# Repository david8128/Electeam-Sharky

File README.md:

# Electeam-Sharky-ESP32

## OrderMe:
1N4728A: caída de voltaje de 3 a 3.5V - CONFIRMAR
## ORDERED:
This is the firmware for the ESP32-DEVKITV1 microcontroller where throttle, break, LCD screen, motor and more systems are integrated.

<!-- TODO Update schematic here -->
> The PCB Kicad folder is located in (controller_bldc_kicad_Sch_PCB/)[https://github.com/david8128/Electeam-Sharky-ESP32/tree/main/controller_bldc_kicad_Sch_PCB]
## Electrical Specifications for the PCB electronics
<!-- Note the reference of nextion in README, 70mA -->
<!-- TODO Document the current and voltage in Current Sensor -->

<!-- TODO Add the MCU and SMPS specs in README-->
#### Power 
Relay for the Operator Presence Control - aka. Death Man Security System (HAT901 12VDC 20A) = 0.96 W
>MOSFET has been considered for de OPC but the consumtion is higher (Using IRF1010N with a )
For this project is used the MCPWM BLDC motor control (hall sensor feedback) example from ESP-IDF library.

As shown in Schematic there were used two [LM2596 DC-DC HW-411](http://tpelectronic.ir/datasheets/20150123144301750.pdf) converters 

#### Battery
When battery is fully charged the voltage is 40.6V. The BMS open the discharging circuit when the battery voltage is under 32V. 

The energy or maximum energetic storage capacity of the battery is 320Wh.

*This modes will be reviewed under the light of the Shell Echo Marathon Competition.*
## Modes

### Acceleration Optimized

### Soft Start

### Manual

Here you have the documentation of the MCPWM-Hall_Sensor example:

## MCPWM BLDC motor control(hall sensor feedback) Example

This example will show you how to use MCPWM module to control bldc motor with hall sensor feedback
 
The following examples uses MCPWM module to control bldc motor and vary its speed continuously

The bldc motor used for testing this code had hall sensor capture sequence of 6-->4-->5-->1-->3-->2-->6-->4--> and so on

IR2103 3-ph bridge driver is used for testing this example code

User needs to make changes according to the motor and gate driver ic used

## Step 1: Pin assignment
* The gpio init function initializes:
	* GPIO19 is assigned as the MCPWM signal for 1H(UH)
	* GPIO18 is assigned as the MCPWM signal for 1L(UL)
	* GPIO17 is assigned as the MCPWM signal for 2H(VH)
	* GPIO16 is assigned as the MCPWM signal for 2L(VL)
	* GPIO15 is assigned as the MCPWM signal for 3H(WH)
	* GPIO14 is assigned as the MCPWM signal for 3L(WL)
	* GPIO23 is assigned as the MCPWM capture signal for Hall A
	* GPIO25 is assigned as the MCPWM capture signal for HALL B
	* GPIO26 is assigned as the MCPWM capture signal for HALL C

## Step 2: Initialize MCPWM
 * You need to set the frequency and duty cycle of MCPWM timer
 * You need to set the MCPWM channel you want to use, and bind the channel with one of the timers
 * You need to set the capture unit, for POS/NEG edge capture
 * Also reversing the hall sensor BIT weight, will make bldc motor rotate CW or CCW

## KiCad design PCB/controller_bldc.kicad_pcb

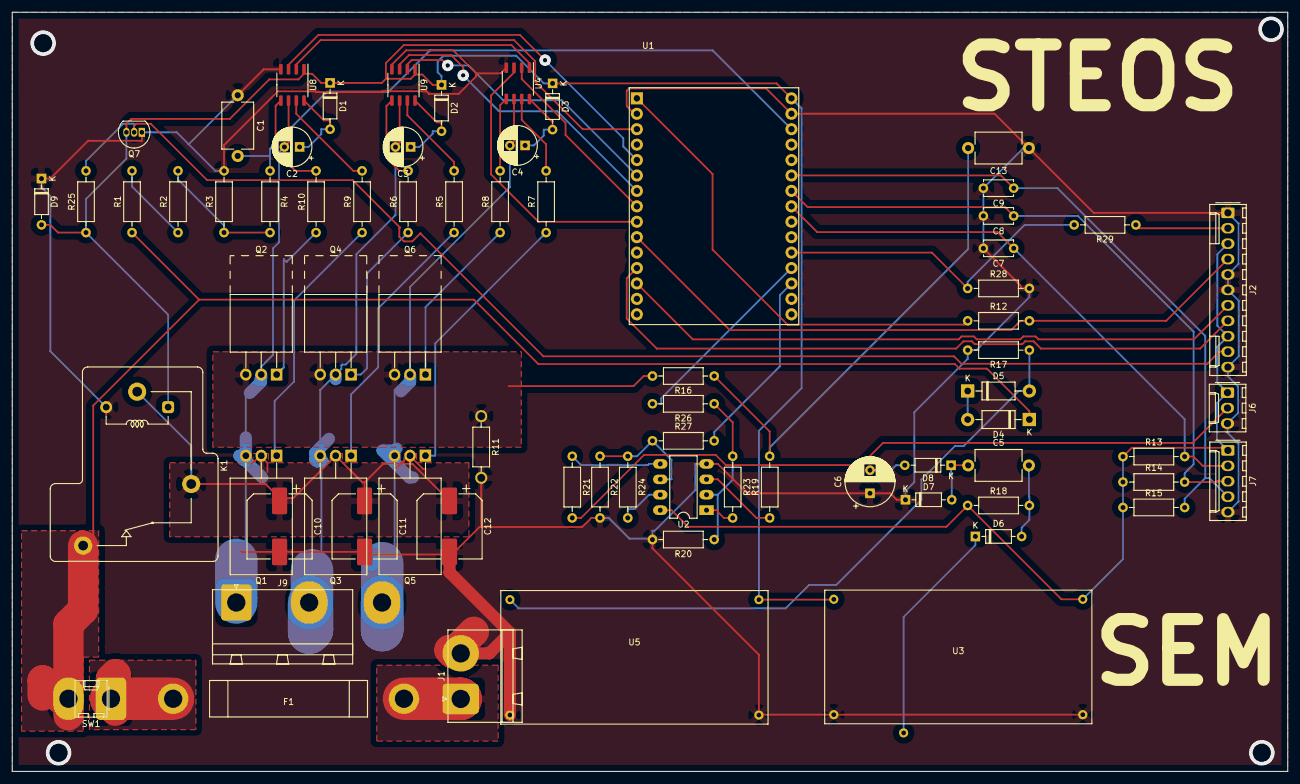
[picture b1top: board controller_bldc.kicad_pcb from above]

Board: 2 copper layers, 210.0 x 125.0 mm, 73 parts (0 on the bottom side), 61 nets.

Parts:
C1: 1uF; C_Disc_D7.5mm_W5.0mm_P10.00mm
C2, C3, C4: 2.2uF; CP_Radial_D6.3mm_P2.50mm
C5: 0.47uF; C_Disc_D7.5mm_W5.0mm_P10.00mm
C6: 47uF; CP_Radial_D8.0mm_P3.80mm
C7, C8, C9: 0.1uF; C_Disc_D4.7mm_W2.5mm_P5.00mm
C10, C11, C12: 220uF; CP_Elec_10x14.3
C13: 0.1uF; C_Disc_D7.5mm_W5.0mm_P10.00mm
D1, D2, D3, D9: 1N4004; D_DO-35_SOD27_P7.62mm_Horizontal
D4, D5: 1N4728A; D_DO-41_SOD81_P10.16mm_Horizontal
D6, D7, D8: 1N4148; D_DO-35_SOD27_P7.62mm_Horizontal
F1: Fuse; Portafusible
J1: Battery Supply; PhoenixContact_GMSTBA_2,5_2-G_1x02_P7.50mm_Horizontal
J2: Conn_01x11_Male; Molex_KK-254_AE-6410-11A_1x11_P2.54mm_Vertical
J6: LM35; Molex_KK-254_AE-6410-03A_1x03_P2.54mm_Vertical
J7: Hall Sensors; Molex_KK-254_AE-6410-05A_1x05_P2.54mm_Vertical
J9: BLDC Motor; PhoenixContact_GMSTBA_2,5_3-G-7,62_1x03_P7.62mm_Horizontal
K1: RAYEX-L90B; Relay_SPST_RAYEX-L90B
Q1, Q3, Q5: IRF1010N; TO-220-3_Horizontal_TabDown
Q2, Q4, Q6: IRF1010N; TO-220-3_Horizontal_TabUp
Q7: PN2222A; TO-92_Inline
R1: 12k; R_Axial_DIN0207_L6.3mm_D2.5mm_P10.16mm_Horizontal
R2, R3: 1k; R_Axial_DIN0207_L6.3mm_D2.5mm_P10.16mm_Horizontal
R4, R16: 10k; R_Axial_DIN0207_L6.3mm_D2.5mm_P10.16mm_Horizontal
R5, R6, R7, R8, R9, R10: 100; R_Axial_DIN0207_L6.3mm_D2.5mm_P10.16mm_Horizontal
R11: 0.1; R_Axial_DIN0207_L6.3mm_D2.5mm_P10.16mm_Horizontal
R12, R13, R14, R15: 1.5k; R_Axial_DIN0207_L6.3mm_D2.5mm_P10.16mm_Horizontal
R17: 5.2k; R_Axial_DIN0207_L6.3mm_D2.5mm_P10.16mm_Horizontal
R18: 220; R_Axial_DIN0207_L6.3mm_D2.5mm_P10.16mm_Horizontal
R19: 4.7k; R_Axial_DIN0207_L6.3mm_D2.5mm_P10.16mm_Horizontal
R20, R21, R22: 15k; R_Axial_DIN0207_L6.3mm_D2.5mm_P10.16mm_Horizontal
R23: 150k; R_Axial_DIN0207_L6.3mm_D2.5mm_P10.16mm_Horizontal
R24: 75k; R_Axial_DIN0207_L6.3mm_D2.5mm_P10.16mm_Horizontal
R25: 2k; R_Axial_DIN0207_L6.3mm_D2.5mm_P10.16mm_Horizontal
R26, R27, R29: 2.5k; R_Axial_DIN0207_L6.3mm_D2.5mm_P10.16mm_Horizontal
R28: 1.2k; R_Axial_DIN0207_L6.3mm_D2.5mm_P10.16mm_Horizontal
SW1: ON_OFF; Molex_KK-254_AE-6410-02A_1x02_P2.54mm_Vertical
U1: ESP32-DEVKITC-32D; MODULE_ESP32-DEVKITC-32D
U2: MC1458P; DIP-8_W7.62mm_LongPads
U3: LM2596SOURCE_Pin2; LM2596DCSourcePin2_Electeam
U4, U8, U9: IR2103; SO-8_3.9x4.9mm_P1.27mm
U5: LM2596SOURCE; LM2596DCSource_Electeam

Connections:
1IN-: R20.1, R23.1, R26.1, U2.2
2IN-: R22.1, R24.1, R27.1, U2.6
36V-Power: C10.1, C11.1, C12.1, K1.11A, K1.11B, Q1.2, Q3.2, Q5.2
+3V3: R12.1, U1.1
+5V: J2.3, J2.9, J6.1, J7.1, R13.1, R14.1, R15.1, R18.1, U2.8, U3.3
+12V: D1.1, D2.1, D3.1, D9.2, K1.A1, Q7.3, R25.1, U1.30, U3.1, U4.1, U5.3, U8.1, U9.1
+36V: D4.1, K1.12, R1.1, SW1.2
-5V: C6.2, D8.2
Brake: J2.4, R12.2, U1.10
Current_Sensor: Q2.3, Q4.3, Q6.3, R11.1, R16.2
Current_Sensor_AO: C13.2, R16.1, R19.2
Current_Sensor_IN: R26.2, U1.19
GND: C1.1, C6.1, C7.2, C8.2, C9.2, C10.2, C11.2, C12.2, C13.1, D7.1, D9.1, J1.2, J2.1, J2.5, J2.6, J2.11, J6.3, J7.5, K1.A2, Q7.1, R3.2, R11.2, R17.2, R20.2, R22.2, R28.2, U1.2, U1.29, U2.4, U3.2, U3.5, U4.4, U5.2, U5.4, U8.4, U9.4
HALL-A: C7.1, J7.2, R13.2, U1.23
HALL-B: C8.1, J7.3, R14.2, U1.24
HALL-C: C9.1, J7.4, R15.2, U1.25
HIN1: U1.3, U8.2
HIN2: U1.6, U9.2
HIN3: U1.8, U4.2
HO1: R9.2, U8.7
HO2: R5.2, U9.7
HO3: R7.2, U4.7
LIN1: U1.5, U8.3
LIN2: U1.7, U9.3
LIN3: U1.9, U4.3
LM35: R27.2, U1.18
LM35-RAW: J6.2, R21.2
LO1: R10.2, U8.5
LO2: R6.2, U9.5
LO3: R8.2, U4.5
unnamed: C2.1, D1.2, U8.8
unnamed: C3.1, D2.2, U9.8
unnamed: C4.1, D3.2, U4.8
unnamed: C5.1, D7.2, D8.1
unnamed: C5.2, D6.2, R18.2
unnamed: D4.2, D5.1
unnamed: D5.2, R17.1, U5.1
unnamed: D6.1, U3.4
unnamed: F1.1, SW1.1
unnamed: F1.2, J1.1
unnamed: Q1.1, R9.1
unnamed: Q2.1, R10.1
unnamed: Q3.1, R5.1
unnamed: Q4.1, R6.1
unnamed: Q5.1, R7.1
unnamed: Q6.1, R8.1
unnamed: R1.2, R2.1
unnamed: R2.2, R3.1, R4.2
unnamed: R19.1, U2.3
unnamed: R21.1, U2.5
unnamed: R23.2, U2.1
unnamed: R24.2, U2.7
OPC_1: J2.10, Q7.2, R25.2
PH1: C2.2, J9.1, Q1.3, Q2.2, U8.6
PH2: C3.2, J9.2, Q3.3, Q4.2, U9.6
PH3: C4.2, J9.3, Q5.3, Q6.2, U4.6
RX-LCD: J2.7, U1.13
TX-LCD: J2.8, U1.12
Throttle: R28.1, R29.2, U1.20
Throttle_Raw: J2.2, R29.1
Voltage_Sensor: C1.2, R4.1, U1.28

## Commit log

2021-04-19 ESP example BLDC motor control
2021-04-19 Version con ADC, se resetea el micro
2021-04-19 Ignore build folder
2021-04-19 Forget about build and change vTaskDelay to 10ms
2021-04-19 Finally motor works only by printing each condition
2021-04-19 Update README.md
    First edition of the README
2021-04-19 Update README.md
    Fix image
2021-04-19 V2.0 with README
2021-04-19 Update README.md
    Adjust of GPIOs
2021-04-20 Added the schematic and PCB design, PCB version V0.3
2021-04-20 PCB v0.5 after autoroute
2021-04-20 Fix in the IR2103 group arrangements inside the PCB
2021-04-21 PCB in v0.7, only relay to change for next and maybe the first tri
2021-04-21 Fix kicad_pcb
2021-04-21 V0.8 with everything except for the relay that should consume less current, 36V-Power is fixed.
2021-04-21 Fix kicad_pcb because of bad merge solve
2021-04-21 Fixed the schematic for the three 220uF capacitors and the connections Connections of MCPWM GPIOs inside the main/*.c were changed to correspond with the schematic
2021-04-21 This is with previous tracks, so 2mm are kept but narrowers are deleted. Version before autorouting
2021-04-21 Deleted unblocked routes to be processed by FreeRouting
2021-04-21 PCB v0.9 after Freerouting, only remaining the verification of the relay. Remember connectors, the fuse and the code for the screen, sensors, current control and also the design and manufacture of th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
2021-04-21 Current sensor added in main/mcpwm...example.c
2021-04-22 The second ADC channel is assigned for the current sensor in main/mcpwm...example.c
2021-04-22 Added the inclued to the main/...c
2021-04-22 Se cambia el nombre del proyecto
2021-04-22 Se adjunta archivo sharky.c
2021-04-22 Se añade un comentario a "sharky.c"
2021-04-24 README updated with electronics specs and the modes feature for firmware
2021-04-24 Firmware: project name and val:pwm_config_frequency fixed
2021-04-24 PCB: Added Amp Op library and changed V & A Sensors
2021-04-27 PCB: Finished with DC Power Sources and Amp. Op. for sensors
2021-04-27 PCB: Footprints changed for DC Sources and the OPC realy
2021-04-27 This fixes PCB and Schematic, closes #5, closes #6, closes #7, closes #8
2021-04-28 PCB Finished, this is version 2.0. Closes #9 and closes #10.
2021-04-29 Firmware: All sensors working just fine
2021-04-29 Firmware moved to the FIRMWARE folder NextionTest folder added
2021-04-29 Due to error of long name NextionTest files changed location
2021-04-29 PCB v1.1 with the res. for throttle
2021-04-29 To be reviewed by Yahico PCB
2021-04-29 Before freerouting
2021-04-29 Sento to Yahiko
2021-04-30 PCB and FIRMWARE changed, see some failures found. Closes #12, closes #13. Tareas realizadas: 0. Corregir afectación de sobrevoltaje en acelerador 1. Mover motor
    Fallas encontradas:
    Desconectando la PCB china disminuye la corriente consumida y funcionan independientes los sensores, sin que V_Sensor altere a los otros sensores.
    Error en acelerador, voltaje de salida del acelerador sin oprimir: 3.2V
    Voltaje de regulación en la segunda fuente de 18V -> Concetar resistencia de consumo en la salida de 100 ohms
2021-04-30 README updated with DC-DC converter's datasheet Closes #11
2021-05-01 PCB working, printing sensors in a good-looking console Fixed the issue with multiple sensors affected when overvoltage in throttle. Closes #16, closes #17, closes #18
2021-05-02 Ignored Build folders everywhere
2021-05-02 Fixing incluiding everything except for TODO and Build Folders
2021-05-02 After refreshing repo, only includes src, PCB. All Build folders are excluded
2021-05-10 PCB v1.1 printed with some errors.
2021-05-10 Deleted .vscode folders
2021-05-10 Added NextionTest working with weather example Fixed #25, closes #27
2021-05-10 Firmware working with Nextion and Sharky sensors. TODO - Check current sensor with motor. TODO - Check battery sensor with motor. TODO - Calculate and display speed. TODO - Calculate and display dist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
2021-05-11 Motor working. Fixed priorities in FreeRTOS tasks.
2021-05-21 Changing all the schematics
2021-05-25 Just before separating folders and branches According to version independence
2021-05-25 Changed folders to 'Diagramas y Esquemas'
2021-05-25 Finalmente se separa la electrónica del firmware
2021-05-25 Primer avance del esquema global
2021-05-25 Ready to create dev/hotfix branches
2021-05-25 Pending if fan is added or not
2021-06-12 Hardware 1.1 working and started with soft+firm-ware Checking and looking for changes to be done inside firmware 1.1. Fan issue still pending.
